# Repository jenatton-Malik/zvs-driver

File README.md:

# ⚡ High-Power ZVS Driver

> A Mazzilli-topology Zero-Voltage-Switching driver — simulated, built and characterized on the bench. Built to understand one of the most elegant self-oscillating circuits in power electronics.

---

## 🎯 Why this project

The ZVS looks almost too simple for what it does: two MOSFETs, a handful of passives, no controller, no microcontroller — and it self-oscillates at exactly the right frequency, switching each transistor at the precise moment its drain voltage crosses zero.

I built it to understand *why* that works. Along the way it also became a working induction heater.

---

## 📐 Specifications

| | |
|---|---|
| **Topology** | Mazzilli ZVS (self-oscillating push-pull) |
| **Switching devices** | 2 × IRFP260N |
| **Rated current** | Up to 18 A |
| **Tested up to** | 8 A |
| **Tank capacitors** | 2 × 0.33 µF double-metallized film, 9.8 A each |
| **Choke** | 100 µH |
| **Input filtering** | 100 µF / 50 V |
| **Gate network** | 470 Ω / 2 W feed resistors, 10 kΩ pulldowns, 12 V zeners, UF4007 clamp diodes |

**On operating frequency:** a ZVS has no fixed switching frequency — it's set by the resonant tank, so it depends entirely on the inductance and impedance of whatever work coil is attached. Change the coil, change the frequency. That's the whole point of the topology.

---

## 🔬 From simulation to hardware

The first step of this project wasn't a soldering iron — it was **LTspice**. Before touching a single component I simulated the full circuit to understand the oscillation mechanism and verify the passive values.

<p align="center"><i>Tank waveform and MOSFET gate drive, simulated in LTspice</i></p>

The simulation files are in [`/simulations`](simulations/).

---

### Breadboard prototype

Before committing to a PCB, a smaller version was built on breadboard using **IRLZ44N** MOSFETs and simple 0.33 µF film capacitors (the mains-filtering type). Lower power, same topology — enough to confirm the circuit oscillates as simulated before spending money on copper.

---

## 🖥️ The board

<p align="center"><i>3D render and copper layout — KiCad</i></p>

Wide, heavy copper pours on the power paths, and generous spacing around the tank — this board carries real current.

<p align="center"><i>Assembled board, top and bottom</i></p>

---

## 📊 Bench characterization

The defining claim of a ZVS is in its name: each MOSFET switches when the voltage across it is at zero, which is why the losses stay so low. So that's what I went looking for on the scope — and confirmed. **Switching happens at the zero crossing**, exactly as designed.

<p align="center"><i>Tank waveform at resonance with a 56 µH work coil</i></p>

The clean, undistorted sine here is the signature of a tank running properly at resonance — and a direct confirmation of the simulated waveform.

<p align="center"><i>Measuring on the bench — simulation and reality side by side</i></p>

**Thermal behaviour:** at just under 10 A, nothing on the board runs hot — not the MOSFETs, not the resistors, not the caps. The components are comfortably sized for the job.

---

## ⚠️ Safety

This circuit handles serious power. Even at the currents shown here, the tank voltage across the coil is far higher than the supply voltage, and the components store enough energy to be genuinely dangerous.

I'm interested in eventually driving high-voltage transformers with it — but only with proper equipment and proper supervision. **Don't reproduce this unless you know exactly what you're doing.**

---

## 📚 References

Built after working through the technical documentation on the topology, along with explainer videos from **ElectroBOOM** and others in the community who've covered this circuit well.

---

## 🛠️ Built with

`LTspice` · `KiCad` · `Oscilloscope characterization` · `Power electronics`

---

## 🏭 Manufacturing

PCBs manufactured by **JLCPCB**, as with every board I've designed.

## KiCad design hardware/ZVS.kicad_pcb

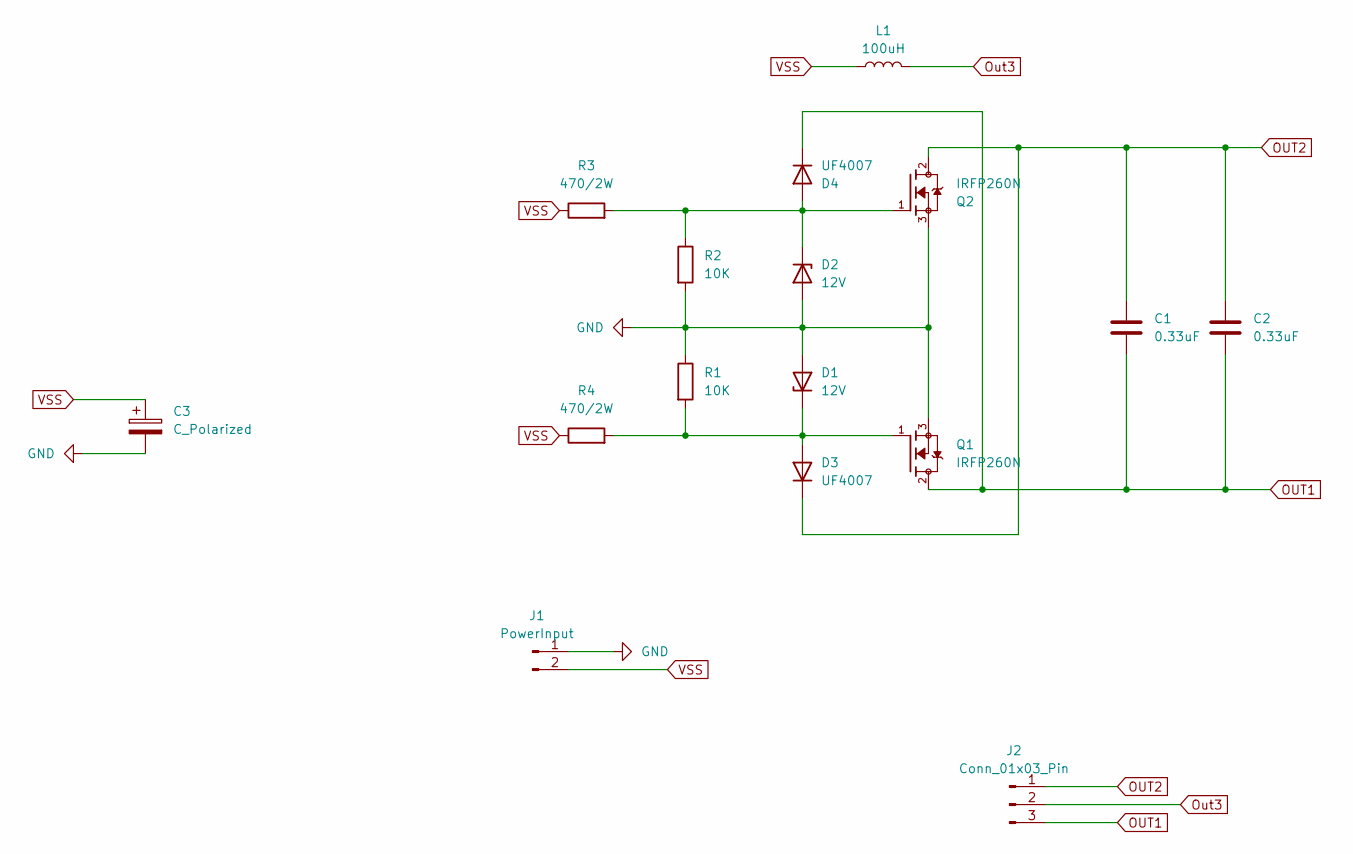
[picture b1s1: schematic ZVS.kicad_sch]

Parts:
C1, C2: 0.33uF; C_Rect_L26.5mm_W11.5mm_P22.50mm_MKS4
C3: C_Polarized; CP_Radial_D8.0mm_P5.00mm
D1, D2: 12V; D_DO-41_SOD81_P10.16mm_Horizontal
D3, D4: UF4007; D_DO-41_SOD81_P10.16mm_Horizontal
J1: PowerInput; TerminalBlock_Phoenix_MKDS-1,5-2-5.08_1x02_P5.08mm_Horizont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
J2: Conn_01x03_Pin; TerminalBlock_Phoenix_MKDS-1,5-4-5.08_1x04_P5.08mm_Horizont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
L1: 100uH; L_Toroid_Vertical_L25.4mm_W14.7mm_P12.20mm_Vishay_TJ5_BigPa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
Q1, Q2: IRFP260N; TO-247-3_Vertical; PARTREV 08/18/10
R1, R2: 10K; R_Axial_DIN0207_L6.3mm_D2.5mm_P7.62mm_Horizontal
R3, R4: 470/2W; R_Axial_DIN0414_L11.9mm_D4.5mm_P15.24mm_Horizontal

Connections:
GND: C3.2, D1.2 (A), D2.2 (A), J1.1, Q1.3, Q2.3, R1.1, R2.2
unnamed: D1.1 (K), D3.2 (A), Q1.1, R1.2, R4.2
unnamed: D2.1 (K), D4.2 (A), Q2.1, R2.1, R3.2
OUT1: C1.2, C2.2, D4.1 (K), J2.3, Q1.2
OUT2: C1.1, C2.1, D3.1 (K), J2.1, Q2.2
Out3: J2.2, L1.2
VSS: C3.1, J1.2, L1.1, R3.1, R4.1

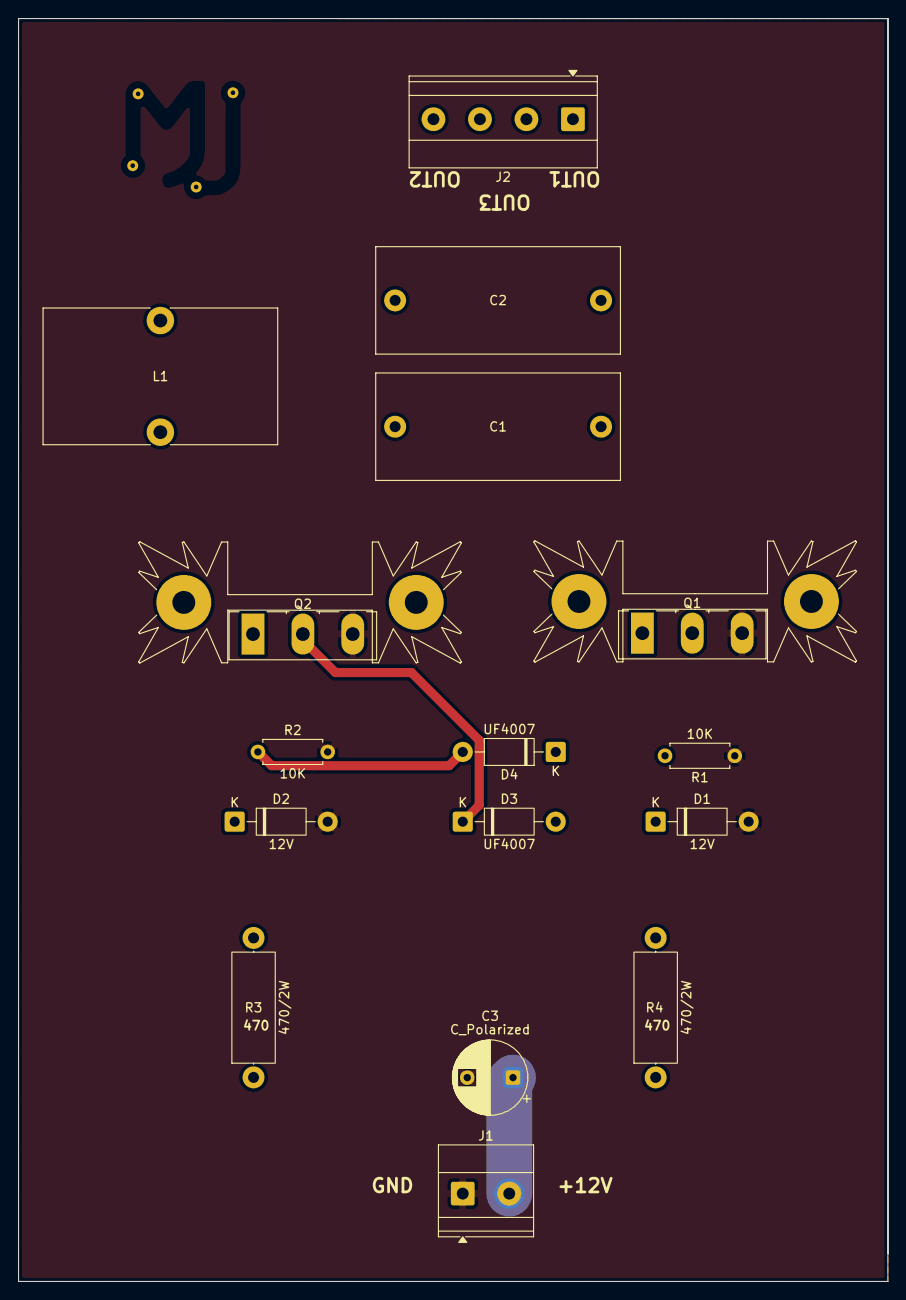
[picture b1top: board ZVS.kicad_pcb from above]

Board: 2 copper layers, 95.0 x 138.0 mm, 16 parts (0 on the bottom side), 7 nets.
